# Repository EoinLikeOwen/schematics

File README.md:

Overview
=========

This repository contains miscellaneous schematics and PCB layouts.  Some are projects I have built (or designed with intent to build, but decided not to build for one reason or another) and others were simple exercises for learning the design tools.

I will try to keep READMEs up-to-date in each project describing which each one is and, if the design was built, how it went.

Currently all design files are for gEDA, but I will likely experiment with other tools soon too.

(Un)license
============

All designs are free to use (I release them to the public domain) - see the file UNLICENSE for more details, including the oh-so-important disclaimer of warrantees.

BOMs
=====

Several projects include BOMs, but not in the traditional pile-of-excel style.  They are Haskell source files, describing the BOM and providing functions to analyze and extract information from them.  They are mainly meant for my own personal use and I may change them without notice, so I'm not going to write any documentation now but feel free to ask for help if you'd like to use them.

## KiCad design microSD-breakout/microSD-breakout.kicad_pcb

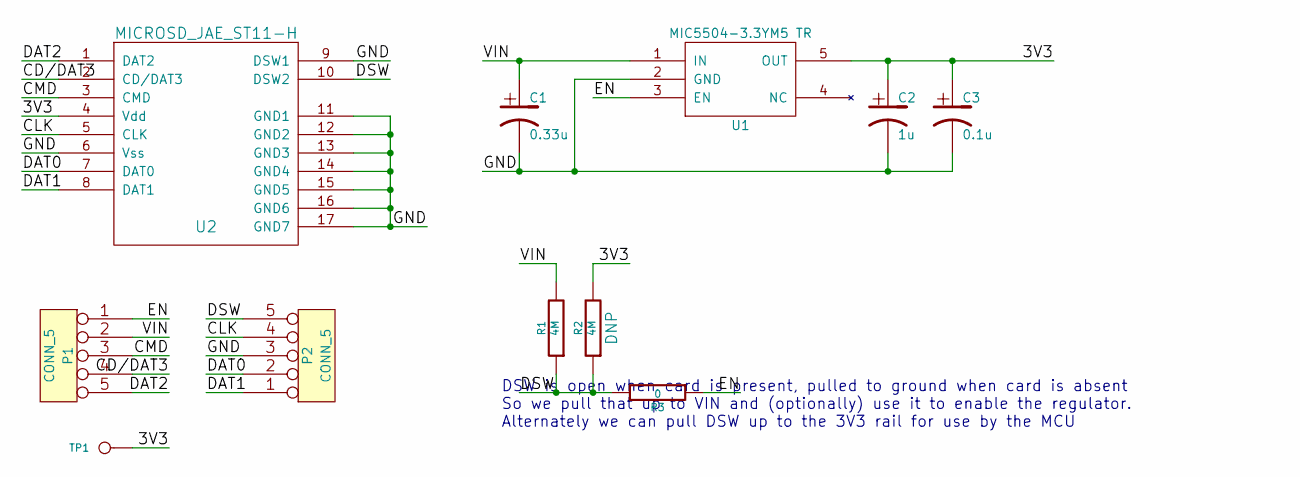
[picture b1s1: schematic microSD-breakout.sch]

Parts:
C1: 0.33u
C2: 1u
C3: 0.1u
P1, P2: CONN_5
R1, R2: 4M
R3: 0
TP1: CONN_1
U1: MIC5504-3.3YM5 TR; SOT23-5
U2: MICROSD_JAE_ST11-H

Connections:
/3V3: C2.1, C3.1, R2.2, TP1.1, U1.5 (OUT), U2.4 (Vdd)
/CD/DAT3: P1.4, U2.2 (CD/DAT3)
/CLK: P2.4, U2.5 (CLK)
/CMD: P1.3, U2.3 (CMD)
/DAT0: P2.2, U2.7 (DAT0)
/DAT1: P2.1, U2.8 (DAT1)
/DAT2: P1.5, U2.1 (DAT2)
/DSW: P2.5, R1.1, R2.1, R3.2, U2.10 (DSW2)
/EN: P1.1, R3.1, U1.3 (EN)
/GND: C1.2, C2.2, C3.2, P2.3, U1.2 (GND), U2.6 (Vss), U2.9 (DSW1), U2.11 (GND1), U2.12 (GND2), U2.13 (GND3), U2.14 (GND4), U2.15 (GND5), U2.16 (GND6), U2.17 (GND7)
/VIN: C1.1, P1.2, R1.2, U1.1 (IN)

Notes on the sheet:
DSW is open when card is present, pulled to ground when card is absent So we pull that up to VIN and (optionally) use it to enable the regulator. Alternately we can pull DSW up to the 3V3 rail for use by the MCU

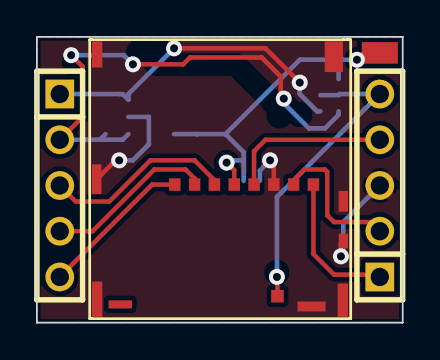
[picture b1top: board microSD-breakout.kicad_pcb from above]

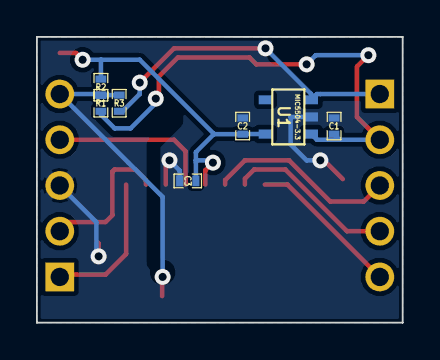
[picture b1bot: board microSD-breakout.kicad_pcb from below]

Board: 2 copper layers, 20.3 x 15.9 mm, 11 parts (7 on the bottom side), 11 nets.

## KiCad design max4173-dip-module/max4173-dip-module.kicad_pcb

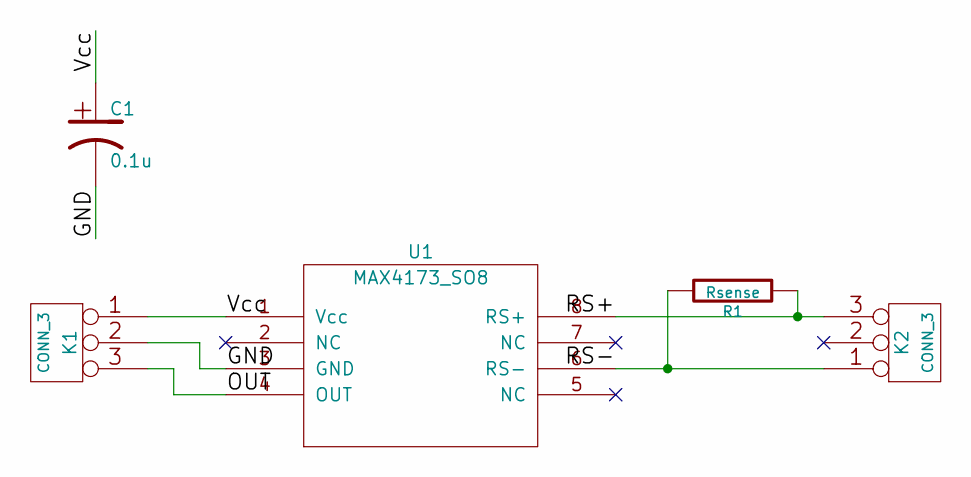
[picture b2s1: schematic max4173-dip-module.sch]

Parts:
C1: 0.1u
K1, K2: CONN_3
R1: Rsense
U1: MAX4173_SO8; SO-8

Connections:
/GND: C1.2, K1.2 (PM), U1.3 (GND)
/OUT: K1.3, U1.4 (OUT)
/RS+: K2.3, R1.1, U1.8 (RS+)
/RS-: K2.1, R1.2, U1.6 (RS-)
/Vcc: C1.1, K1.1, U1.1 (Vcc)

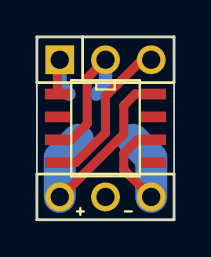
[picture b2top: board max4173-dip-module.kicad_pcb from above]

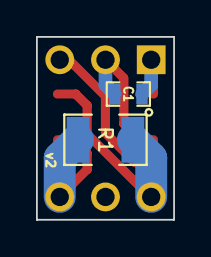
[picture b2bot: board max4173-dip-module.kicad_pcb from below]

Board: 2 copper layers, 7.6 x 10.2 mm, 5 parts (2 on the bottom side), 5 nets.

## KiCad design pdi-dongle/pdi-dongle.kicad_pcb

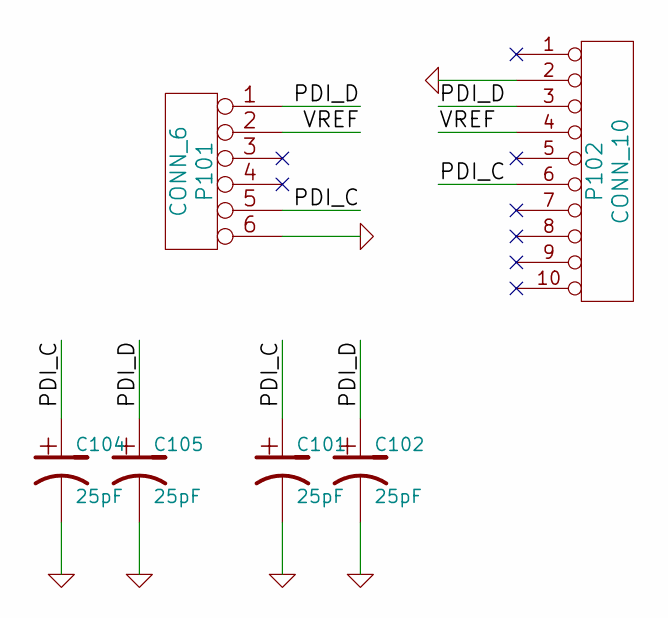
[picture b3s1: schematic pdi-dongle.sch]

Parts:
C101, C102, C104, C105: 25pF
P101: CONN_6
P102: CONN_10

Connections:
/PDI_C: C101.1, C104.1, P101.5, P102.6
/PDI_D: C102.1, C105.1, P101.1, P102.3
/VREF: P101.2, P102.4
GND: C101.2, C102.2, C104.2, C105.2, P101.6, P102.2

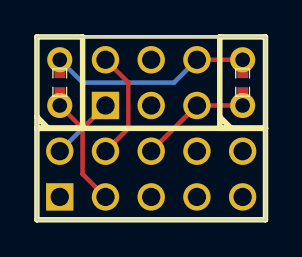
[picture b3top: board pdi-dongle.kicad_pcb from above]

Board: 2 copper layers, 12.7 x 10.2 mm, 6 parts (0 on the bottom side), 4 nets.

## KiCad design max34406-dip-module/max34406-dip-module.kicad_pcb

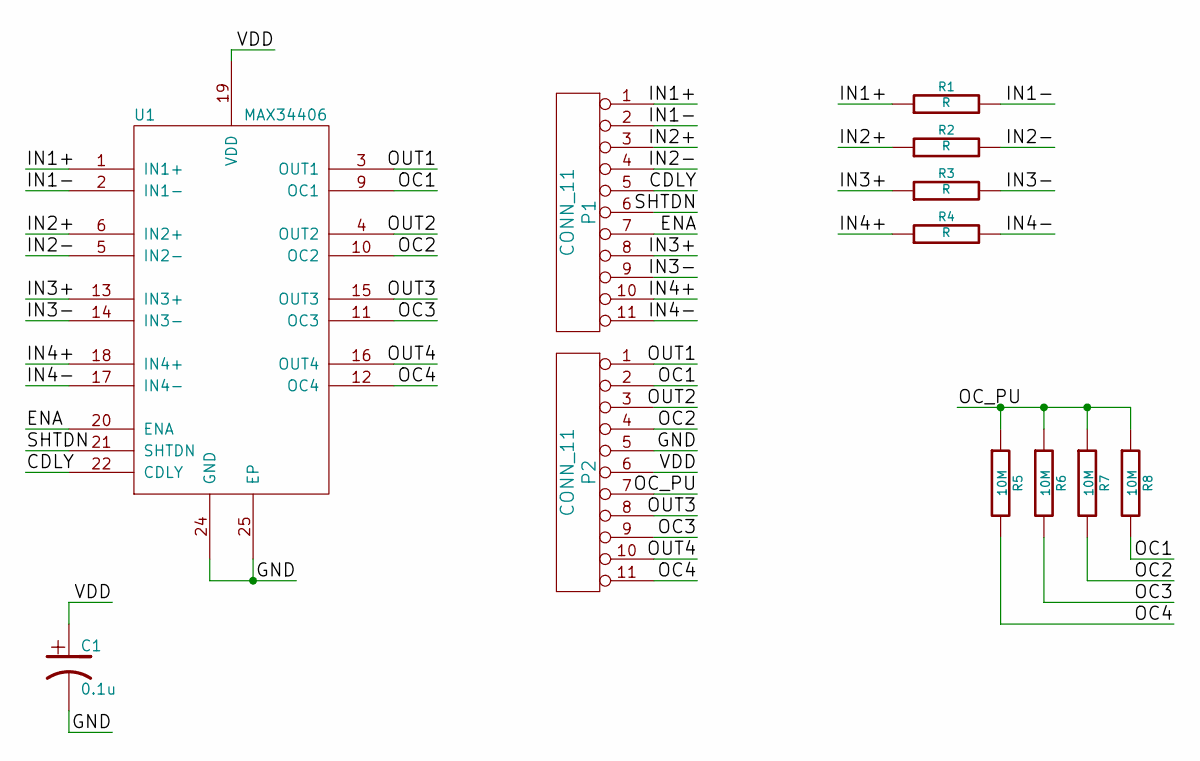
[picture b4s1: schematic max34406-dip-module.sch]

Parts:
C1: 0.1u
P1, P2: CONN_11
R1, R2, R3, R4: R
R5, R6, R7, R8: 10M
U1: MAX34406; QFN24_EP

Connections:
/CDLY: P1.5, U1.22 (CDLY)
/ENA: P1.7, U1.20 (ENA)
/GND: C1.2, P2.5, U1.24 (GND), U1.25 (EP)
/IN1+: P1.1, R1.1, U1.1 (IN1+)
/IN1-: P1.2, R1.2, U1.2 (IN1-)
/IN2+: P1.3, R2.1, U1.6 (IN2+)
/IN2-: P1.4, R2.2, U1.5 (IN2-)
/IN3+: P1.8, R3.1, U1.13 (IN3+)
/IN3-: P1.9, R3.2, U1.14 (IN3-)
/IN4+: P1.10, R4.1, U1.18 (IN4+)
/IN4-: P1.11, R4.2, U1.17 (IN4-)
/OC1: P2.2, R8.2, U1.9 (OC1)
/OC2: P2.4, R7.2, U1.10 (OC2)
/OC3: P2.9, R6.2, U1.11 (OC3)
/OC4: P2.11, R5.2, U1.12 (OC4)
/OC_PU: P2.7, R5.1, R6.1, R7.1, R8.1
/OUT1: P2.1, U1.3 (OUT1)
/OUT2: P2.3, U1.4 (OUT2)
/OUT3: P2.8, U1.15 (OUT3)
/OUT4: P2.10, U1.16 (OUT4)
/SHTDN: P1.6, U1.21 (SHTDN)
/VDD: C1.1, P2.6, U1.19 (VDD)

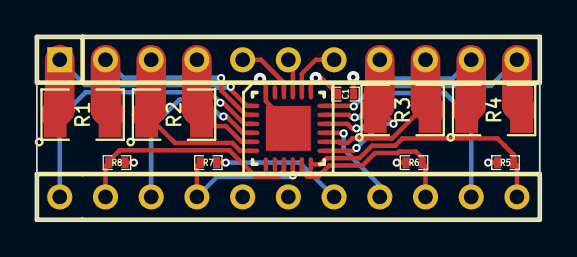
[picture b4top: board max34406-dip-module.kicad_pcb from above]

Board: 4 copper layers, 27.9 x 10.2 mm, 12 parts (0 on the bottom side), 22 nets.

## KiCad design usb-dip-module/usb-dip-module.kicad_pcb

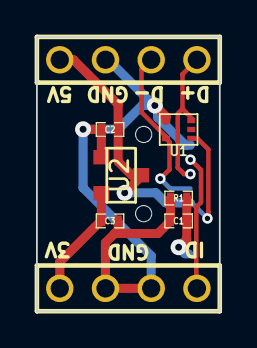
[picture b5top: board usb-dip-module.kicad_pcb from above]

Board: 2 copper layers, 10.2 x 15.2 mm, 9 parts (1 on the bottom side), 7 nets.

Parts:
C1: 4.7nF; SM0402_c
C2: 0.1uF; SM0402_c
C3: 1uF; SM0402_c
CON1: USB-MINI-B; USB_MINI_B
P1, P2: CONN_4; PIN_ARRAY_4x1
R1: 1M; SM0402_r
U1: TPD2E001IDRLRQ1; SOT553
U2: AAT3220; SC59

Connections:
D+: CON1.3, P2.4, U1.3
D-: CON1.2, P2.3, U1.5
GND: C1.2, C2.2, C3.2, CON1.5, P1.2, P1.3, P2.2, R1.2, U1.4, U2.1
ID: CON1.4, P1.4
unnamed: C1.1, CON1.6, R1.1
VBUS: C2.1, CON1.1, P2.1, U1.1, U2.3
VREG: C3.1, P1.1, U2.2

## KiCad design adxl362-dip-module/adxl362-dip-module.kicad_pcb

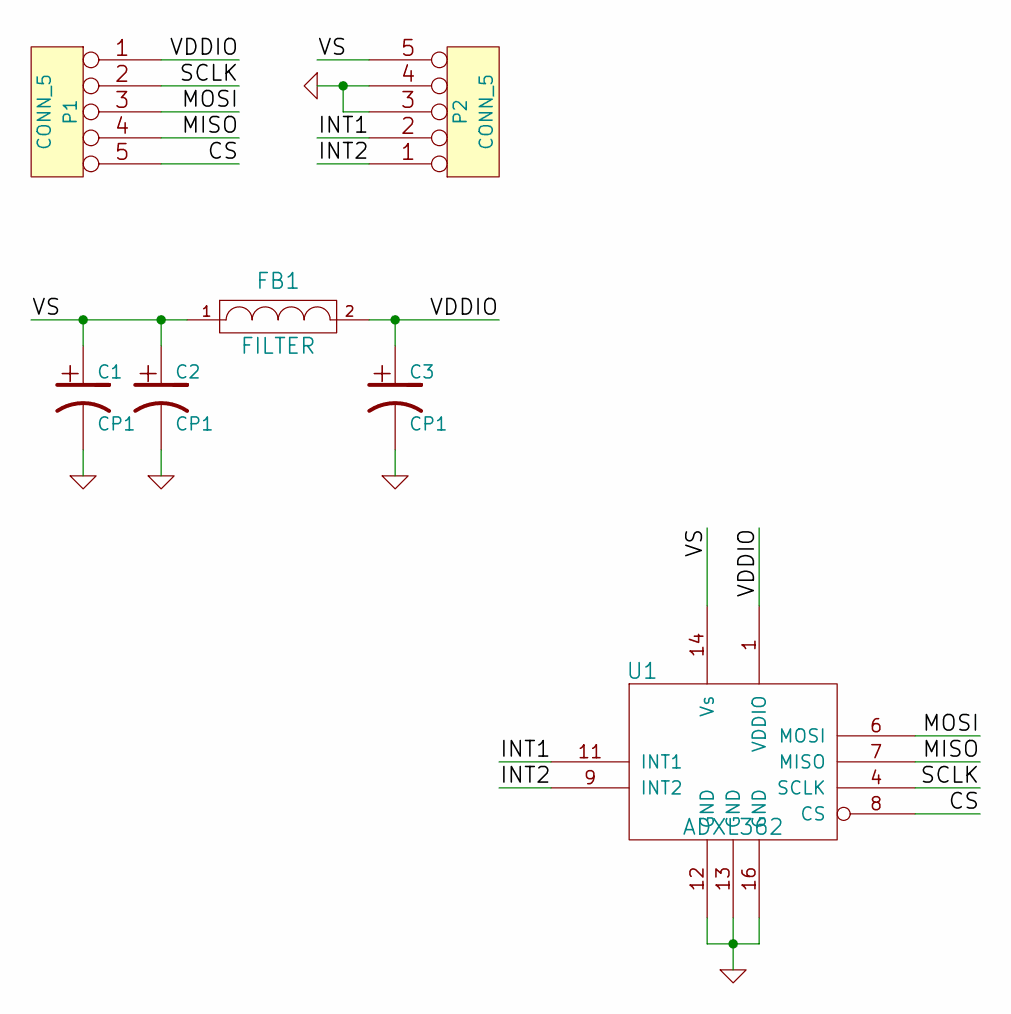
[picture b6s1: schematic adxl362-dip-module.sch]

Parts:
C1, C2, C3: CP1
FB1: FILTER
P1, P2: CONN_5
U1: ADXL362

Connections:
/CS: P1.5, U1.8 (CS)
/INT1: P2.2, U1.11 (INT1)
/INT2: P2.1, U1.9 (INT2)
/MISO: P1.4, U1.7 (MISO)
/MOSI: P1.3, U1.6 (MOSI)
/SCLK: P1.2, U1.4 (SCLK)
/VDDIO: C3.1, FB1.2, P1.1, U1.1 (VDDIO)
/VS: C1.1, C2.1, FB1.1, P2.5, U1.14 (Vs)
GND: C1.2, C2.2, C3.2, P2.3, P2.4, U1.12 (GND), U1.13 (GND), U1.16 (GND)

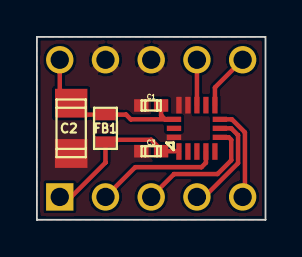
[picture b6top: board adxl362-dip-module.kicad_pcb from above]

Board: 2 copper layers, 12.7 x 10.2 mm, 7 parts (0 on the bottom side), 9 nets.

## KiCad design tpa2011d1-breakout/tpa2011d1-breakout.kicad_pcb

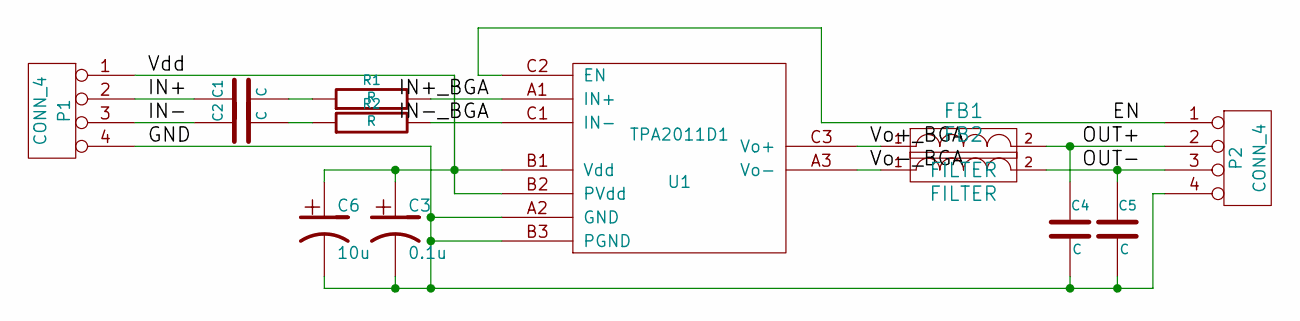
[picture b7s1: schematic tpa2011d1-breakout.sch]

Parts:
C1, C2, C4, C5: C
C3: 0.1u
C6: 10u
FB1, FB2: FILTER
P1, P2: CONN_4
R1, R2: R
U1: TPA2011D1; MODULE

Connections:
/EN: P2.1, U1.C2 (EN)
/GND: C3.2, C4.2, C5.2, C6.2, P1.4, P2.4, U1.A2 (GND), U1.B3 (PGND)
/IN+: C1.1, P1.2
/IN+_BGA: R1.2, U1.A1 (IN+)
/IN-: C2.1, P1.3
/IN-_BGA: R2.2, U1.C1 (IN-)
/OUT+: C4.1, FB1.2, P2.2
/OUT-: C5.1, FB2.2, P2.3
/Vdd: C3.1, C6.1, P1.1, U1.B1 (Vdd), U1.B2 (PVdd)
/Vo+_BGA: FB1.1, U1.C3 (Vo+)
/Vo-_BGA: FB2.1, U1.A3 (Vo-)
unnamed: C2.2, R2.1
unnamed: C1.2, R1.1

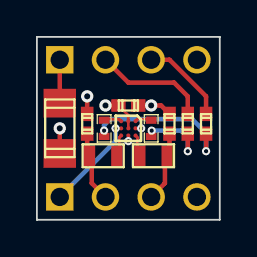
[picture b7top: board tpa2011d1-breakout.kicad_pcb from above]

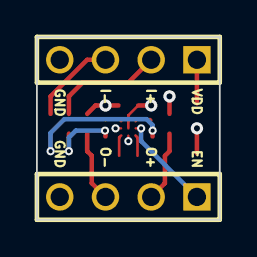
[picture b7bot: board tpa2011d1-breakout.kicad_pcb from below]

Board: 4 copper layers, 10.2 x 10.2 mm, 13 parts (2 on the bottom side), 13 nets.

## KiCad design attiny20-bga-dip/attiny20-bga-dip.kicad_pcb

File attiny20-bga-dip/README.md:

A simple DIP adapter board for a small BGA part (ATtiny20).
Just something I threw together to see how hard it is to solder
parts like this.

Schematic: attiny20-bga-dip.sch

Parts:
C1: CP1
FB1: FILTER
P1, P2: CONN_7
P3: TC2030-IDC
U1: ATTINY20-CCU; UFBGA-15

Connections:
/GND: C1.2, P1.7, P3.6, U1.D2, U1.D3
/PA0: P1.6, U1.D1
/PA1: P1.5, U1.C3
/PA2: P1.4, U1.C2
/PA3: P1.3, U1.C1
/PA4: P1.2, U1.B1
/PA5: P1.1, U1.A2
/PA6: P2.7, U1.A3
/PA7: P2.6, U1.B2
/PB0: P2.2, P3.3, U1.C4
/PB1: P2.3, P3.1, U1.B3
/PB2: P2.5, U1.A4
/PB3: P2.4, P3.5, U1.B4
/VCC: FB1.1, P2.1, P3.2
unnamed: C1.1, FB1.2, U1.D4

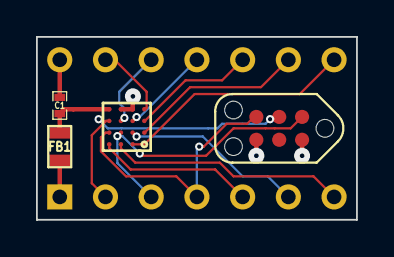
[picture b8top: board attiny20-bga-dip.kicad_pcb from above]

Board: 4 copper layers, 17.8 x 10.2 mm, 6 parts (0 on the bottom side), 15 nets.

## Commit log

2013-05-17 a couple small schematics
2013-05-17 Finished tracing flood light and started new design
    new design will probably end up as a rs-485 controlled light based on
    ATTiny2313A
2013-05-17 a bit more work on the dmx led schematic
2013-08-07 Learn you some gEDA for great skull-crushing frustration!
    What the heck, throwing it all in the bucket.
2013-08-12 simple little pcb for isp header on a breadboard
2013-08-12 gitignore for gEDA stuff
2013-08-12 added several symbols and footprints
2013-08-12 schematic for an ATmega256RFR2 dev board
2013-08-12 Made a QFN64 footprint
2013-08-12 added footprint for 2450FB15L0001 balun/filter
2013-08-13 finished footprints for atmega rfr2 target board
2013-08-15 at86rf233 breakout pcb, as ordered last night
    probably should've waited to order... used wrong transmission line calculator, should've used a 'coplanar waveguide w/ground' calculation rather than microstrip.
2013-08-16 fixed transmission line on at86rf breakout
    also improved ground connections a bit
2013-09-02 new xmega e5 schematic for qfp package
2013-09-02 BOMs for a couple boards
2013-09-02 minor improvements to xmega e5 board
2013-09-02 dedicated analog ground trace on xmega e5 board
2013-09-02 improving routing and ground connections on xmega e5 board
2013-09-02 regenerated gerbers for xmega e5 board
2013-09-02 removed some gerbers that didn't really belong
    they were just a demonstration of some weird behavior with rotating footprints in gEDA
2013-09-02 .gitignore
2013-09-02 README, etc
2013-09-02 moved LED floodlight schematics into subdirs
    also added READMEs and made some minor corrections to the schematics
2013-09-02 renamed gEDA support dirs
2013-09-02 README more
2013-09-02 BOM for omega e5 board
2013-09-08 notes about tree power section schematic
2013-09-08 added a simple pull-up network DIP module pcb
2013-09-14 footprint for Xbee without the overhang
2014-01-19 breakout board for FTDI FT234DX
    assembled very quickly, don't hate ;)
    (also my first non-tutorial kicad project)
2014-01-19 readme update
2014-01-19 README more!
2014-01-19 updated some READMEs
2014-01-19 minor BOM code changes
2014-01-21 new version of XMEGA A4U board
    adds AVcc conditioning, a crystal, a USB port and a 3.3v regulator.
2014-01-21 adjusted a drill position i didn't like
2014-01-21 moar holes plz
    (added more ground connections on a4u board, around areas that i suspect are especially sensitive or noisy... no idea whether it's actually a valuable thing to do though, i'm just cargo culting here 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
2014-01-22 new board - simple usb DIP module
2014-01-22 BOMs for new boards
2014-01-24 threw together a little picobuck clone
    had some extra space on a stencil order coming up :)
2014-01-25 added BOM for picobuck clone
2014-02-13 squeezed USB DIP module 100 mils narrower
    SMT stencils from previous version should still work, though the
    USB connector shield is very slightly narrower to clear the header
    through-holes (IIRC, i only had to trim about 1 mil off so it
    should be fine)
2014-02-13 fixed a mistake on XMEGA A4U board
    one of the crystal's ground pads was not connected on the schematic
    (the lines were "touching" but not actually connected)
2014-02-13 more .gitignore
2014-02-13 a small breakout for the SOT25 footprint
    i did this one a while back (I've already got the order back
    from OSH Park) but apparently didn't commit it.
2014-02-13 a new version of the xmega e5 board
2014-02-17 fixed dfn12 pad spacing
2014-02-17 simplified and shrunk ft234xd board
2014-02-17 embiggened pin header drill holes on A4U board...
    ... and added a VREG-VCC jumper
2014-02-20 fixed xmega a4u pad... again...
2014-02-21 un-.gitignored cache.lib files
2014-04-22 moved some markings on ft234xd board
2014-05-27 added a small adapter board
    probably of interest to no-one except me.
2014-07-19 added a DIP adapter board for ATtiny20
2014-07-19 more parts
2014-07-19 plotted attiny20 board
2014-07-19 merged NPTH drill holes into main DRL file
2014-07-19 adapter board for an RTC with integrated crystal
2014-07-19 a breakout board for a class-D amplifier IC
2014-07-19 changed usb DIP module to use what should be OSH Park-friendly NPTH's
2014-07-19 more NPTH revisions
2014-07-19 making attiny20 board OSH Park-friendly
2014-07-19 another missing layer
2014-07-19 fixing another board up to order
2014-07-19 preparing another board for ordering
2014-07-20 another little DIP board
2014-07-31 sigh... another borked order. removed planes, rerouted, let's try this again.
2014-08-02 another little board
2014-08-02 minor update to max4173 silkscreen
2014-08-02 another current-sense amp board
2014-08-02 embiggening a current-sense resistor pad
2014-08-02 oops, let's add the parts for the last 2 boards
2014-08-02 grr... "bottom silk screen; image [can't be blank]"
2014-08-02 added a uSD breakout
2014-08-03 embiggened pads a bit
2014-08-13 new version of the PDI adapter board
2014-08-15 fixed pin numbering error on MAX4173 board
2015-08-27 changed some stuff. a long time ago, so i don't remember what.
2015-08-27 changed some other stuff... this will probably conflict
2015-08-27 brute force merge-conflict non-resolution...
    i don't remember either of these conflicting changes, guess i'll just keep both
    till i have time to look at them
